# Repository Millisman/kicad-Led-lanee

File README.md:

# kicad-Led-lanee
Cheap LED lamp in the form of a narrow strip. Single layer PCB design for aluminum die.

Cheap LEDs XL-2835UWC-02

Current < 1.5A

Voltage ~12V DC

Factory JLC

Current < 1.5A

Voltage +/- 12V DC

Factory JLC

License MIT

If you need a unique design of lamps and other complex circuit boards, hardware design, reproduction, reverse engineering, repair - write to me at contact@arduino.uno

Sergey Kostyanoy (с) 2023

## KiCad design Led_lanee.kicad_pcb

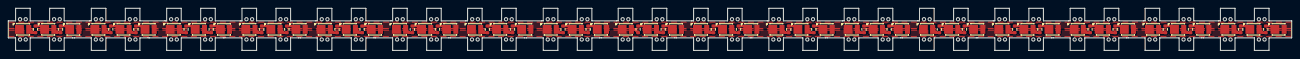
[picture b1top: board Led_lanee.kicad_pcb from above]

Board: 2 copper layers, 316.9 x 10.4 mm, 85 parts (0 on the bottom side), 70 nets.

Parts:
D1, D2, D3, D4, D5, D6, D7, D8, D9, D10, D11, D12, D13, D14, D15, D16, D17, D18, D19, D20, D21, D22, D23, D24, D25, D26, D27, D28, D29, D30, D31, D32, D33, D34, D35, D36, D37, D38, D39, D40, D41, D42, D43, D44, D45, D46, D47, D48, D49, D50, D51: LED; LED-SMD_L3.5-W2.8-RD_1.25T-2PWT
R1, R2, R3, R4, R5, R6, R7, R8, R9, R10, R11, R12, R13, R14, R15, R16, R17, R18, R19, R20, R21, R22, R23, R24, R25, R26, R27, R28, R29, R30, R31, R32, R33, R34: 47; R_0603_1608Metric

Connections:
/12V0: D1.2 (A), D4.2 (A), D7.2 (A), D10.2 (A), D13.2 (A), D16.2 (A), D19.2 (A), D22.2 (A), D25.2 (A), D28.2 (A), D31.2 (A), D34.2 (A), D37.2 (A), D40.2 (A), D43.2 (A), D46.2 (A), D49.2 (A)
/GND: D3.1 (K), D6.1 (K), D9.1 (K), D12.1 (K), D15.1 (K), D18.1 (K), D21.1 (K), D24.1 (K), D27.1 (K), D30.1 (K), D33.1 (K), D36.1 (K), D39.1 (K), D42.1 (K), D45.1 (K), D48.1 (K), D51.1 (K)
unnamed: D1.1 (K), R1.1
unnamed: D2.1 (K), R2.1
unnamed: D2.2 (A), R1.2
unnamed: D3.2 (A), R2.2
unnamed: D4.1 (K), R3.1
unnamed: D5.1 (K), R4.1
unnamed: D5.2 (A), R3.2
unnamed: D6.2 (A), R4.2
unnamed: D7.1 (K), R5.1
unnamed: D8.1 (K), R6.1
unnamed: D8.2 (A), R5.2
unnamed: D9.2 (A), R6.2
unnamed: D10.1 (K), R7.1
unnamed: D11.1 (K), R8.1
unnamed: D11.2 (A), R7.2
unnamed: D12.2 (A), R8.2
unnamed: D13.1 (K), R9.1
unnamed: D14.1 (K), R10.1
unnamed: D14.2 (A), R9.2
unnamed: D15.2 (A), R10.2
unnamed: D16.1 (K), R11.1
unnamed: D17.1 (K), R12.1
unnamed: D17.2 (A), R11.2
unnamed: D18.2 (A), R12.2
unnamed: D19.1 (K), R13.1
unnamed: D20.1 (K), R14.1
unnamed: D20.2 (A), R13.2
unnamed: D21.2 (A), R14.2
unnamed: D22.1 (K), R15.1
unnamed: D23.1 (K), R16.1
unnamed: D23.2 (A), R15.2
unnamed: D24.2 (A), R16.2
unnamed: D25.1 (K), R17.1
unnamed: D26.1 (K), R18.1
unnamed: D26.2 (A), R17.2
unnamed: D27.2 (A), R18.2
unnamed: D28.1 (K), R19.1
unnamed: D29.1 (K), R20.1
unnamed: D29.2 (A), R19.2
unnamed: D30.2 (A), R20.2
unnamed: D31.1 (K), R21.1
unnamed: D32.1 (K), R22.1
unnamed: D32.2 (A), R21.2
unnamed: D33.2 (A), R22.2
unnamed: D34.1 (K), R23.1
unnamed: D35.1 (K), R24.1
unnamed: D35.2 (A), R23.2
unnamed: D36.2 (A), R24.2
unnamed: D37.1 (K), R25.1
unnamed: D38.1 (K), R26.1
unnamed: D38.2 (A), R25.2
unnamed: D39.2 (A), R26.2
unnamed: D40.1 (K), R27.1
unnamed: D41.1 (K), R28.1
unnamed: D41.2 (A), R27.2
unnamed: D42.2 (A), R28.2
unnamed: D43.1 (K), R29.1
unnamed: D44.1 (K), R30.1
unnamed: D44.2 (A), R29.2
unnamed: D45.2 (A), R30.2
unnamed: D46.1 (K), R31.1
unnamed: D47.1 (K), R32.1
unnamed: D47.2 (A), R31.2
unnamed: D48.2 (A), R32.2
unnamed: D49.1 (K), R33.1
unnamed: D50.1 (K), R34.1
unnamed: D50.2 (A), R33.2
unnamed: D51.2 (A), R34.2

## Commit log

2023-06-16 photo/model
